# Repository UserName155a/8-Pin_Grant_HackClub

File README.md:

Log:

11/10 ~23:00 - 11/11 ~00:40 : Working on Joystick project to use as a mouse cursor controller 

11/11 ~9:XX - 11/11 12:XX : Figuring out what parts to use and some wiring on schematics 

11/11 2:04 - 2:36 : Mapped out schematics and finalized

11/12 20:22 - 23:45 : Trying to figure out how PCB editor works

11/13 22:00 - 13:37 : Redesigned power management portion of sch

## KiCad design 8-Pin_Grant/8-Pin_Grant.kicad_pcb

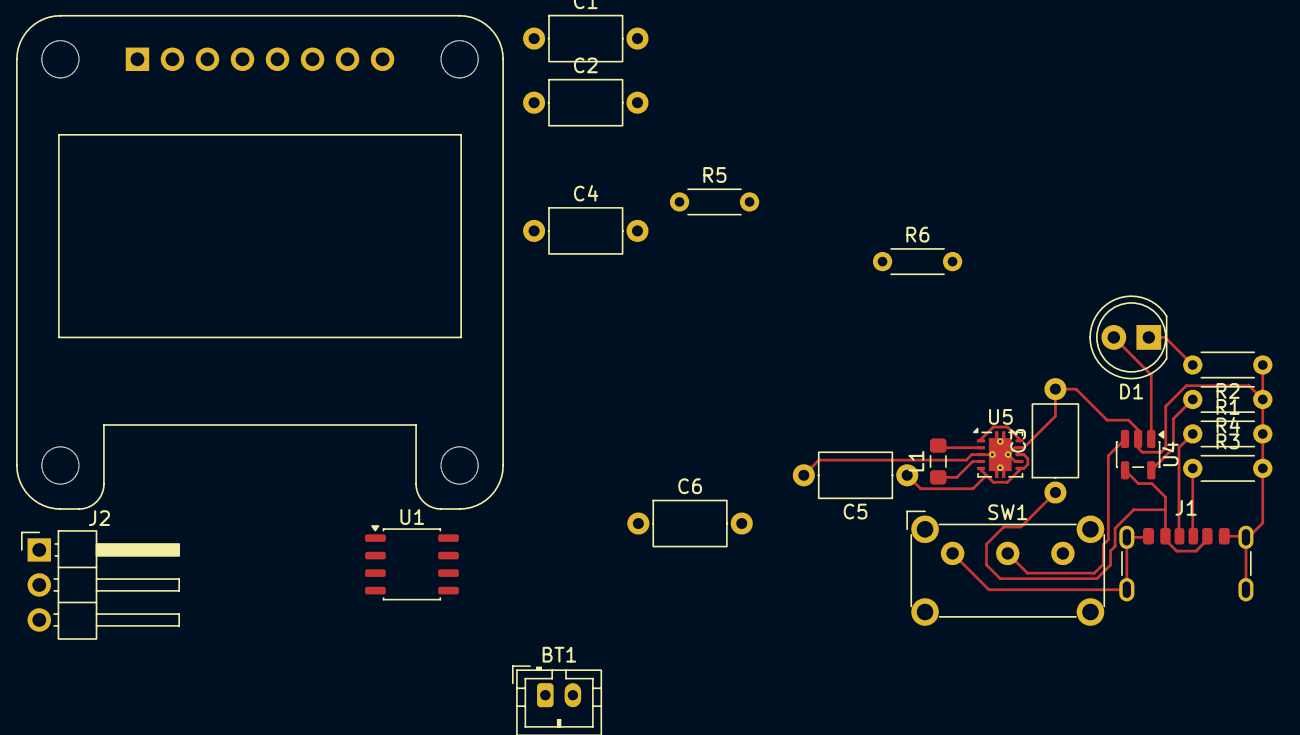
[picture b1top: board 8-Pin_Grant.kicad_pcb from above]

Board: 2 copper layers, 22 parts (0 on the bottom side), 15 nets.

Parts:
BT1: Battery_Cell; JST_PH_B2B-PH-K_1x02_P2.00mm_Vertical
C1, C2: 1uF; C_Axial_L5.1mm_D3.1mm_P7.50mm_Horizontal
C3, C4: 4.7uF; C_Axial_L5.1mm_D3.1mm_P7.50mm_Horizontal
C5: 10uF; C_Axial_L5.1mm_D3.1mm_P7.50mm_Horizontal
C6: 22uF; C_Axial_L5.1mm_D3.1mm_P7.50mm_Horizontal
D1: LED; LED_D5.0mm
J1: USB_C_Receptacle_PowerOnly_6P; USB_C_Receptacle_GCT_USB4125-xx-x-0190_6P_TopMnt_Horizontal
J2: Conn_01x03; PinHeader_1x03_P2.54mm_Horizontal
L1: L; L_0805_2012Metric_Pad1.05x1.20mm_HandSolder
R1, R3: 5.1k; R_Axial_DIN0204_L3.6mm_D1.6mm_P5.08mm_Horizontal
R2: 220; R_Axial_DIN0204_L3.6mm_D1.6mm_P5.08mm_Horizontal
R4: 2k; R_Axial_DIN0204_L3.6mm_D1.6mm_P5.08mm_Horizontal
R5, R6: 4.7k; R_Axial_DIN0204_L3.6mm_D1.6mm_P5.08mm_Horizontal
SW1: SW_SPDT; SW_E-Switch_EG1224_SPDT_Angled
U1: CH32V003JxMx; JEITA_SOIC-8_3.9x4.9mm_P1.27mm
U2: ER_OLEDM0.91_1x-I2C; Adafruit_SSD1306
U4: MCP73831-2-OT; SOT-23-5
U5: TPS63001; Texas_DRC0010J_ThermalVias

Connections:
GND: BT1.2 (-), C1.2, C2.1, C3.2, C4.2, C5.2, C6.2, J1.A12 (GND), J1.B12 (GND), J1.SH (SHIELD), J2.3, R1.2, R2.1, R3.2, R4.1, SW1.1 (A), U1.2 (VSS), U2.1 (GND), U4.2 (V_{SS}), U5.3 (PGND), U5.7 (PS/SYNC), U5.9 (GND), U5.11 (PGND)
unnamed: BT1.1 (+), C4.1, SW1.2 (B), U4.3 (V_{BAT})
unnamed: D1.2 (A), U4.1 (STAT)
unnamed: D1.1 (K), R2.2
unnamed: J1.A5 (CC1), R1.1
unnamed: J1.B5 (CC2), R3.1
unnamed: C1.1, C2.2, C6.1, J2.1, R5.1, R6.1, U1.4 (VDD), U2.2 (VCC), U5.1 (VOUT), U5.10 (FB)
unnamed: J2.2, U1.8 (PD1/PD4/PD5)
unnamed: C5.1, SW1.3 (C), U5.5 (VIN), U5.6 (EN), U5.8 (VINA)
unnamed: R6.2, U1.5 (PC1), U2.4 (SDA)
unnamed: R5.2, U1.6 (PC2), U2.3 (SCL)
unnamed: R4.2, U4.5 (PROG)
unnamed: C3.1, J1.A9 (VBUS), J1.B9 (VBUS), U4.4 (V_{DD})
unnamed: L1.1, U5.4 (L1)
unnamed: L1.2, U5.2 (L2)
